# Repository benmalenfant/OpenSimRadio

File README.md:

# OpenSimRadio
Open sourced radio stack for flight simulation (Work in progress, not finished)

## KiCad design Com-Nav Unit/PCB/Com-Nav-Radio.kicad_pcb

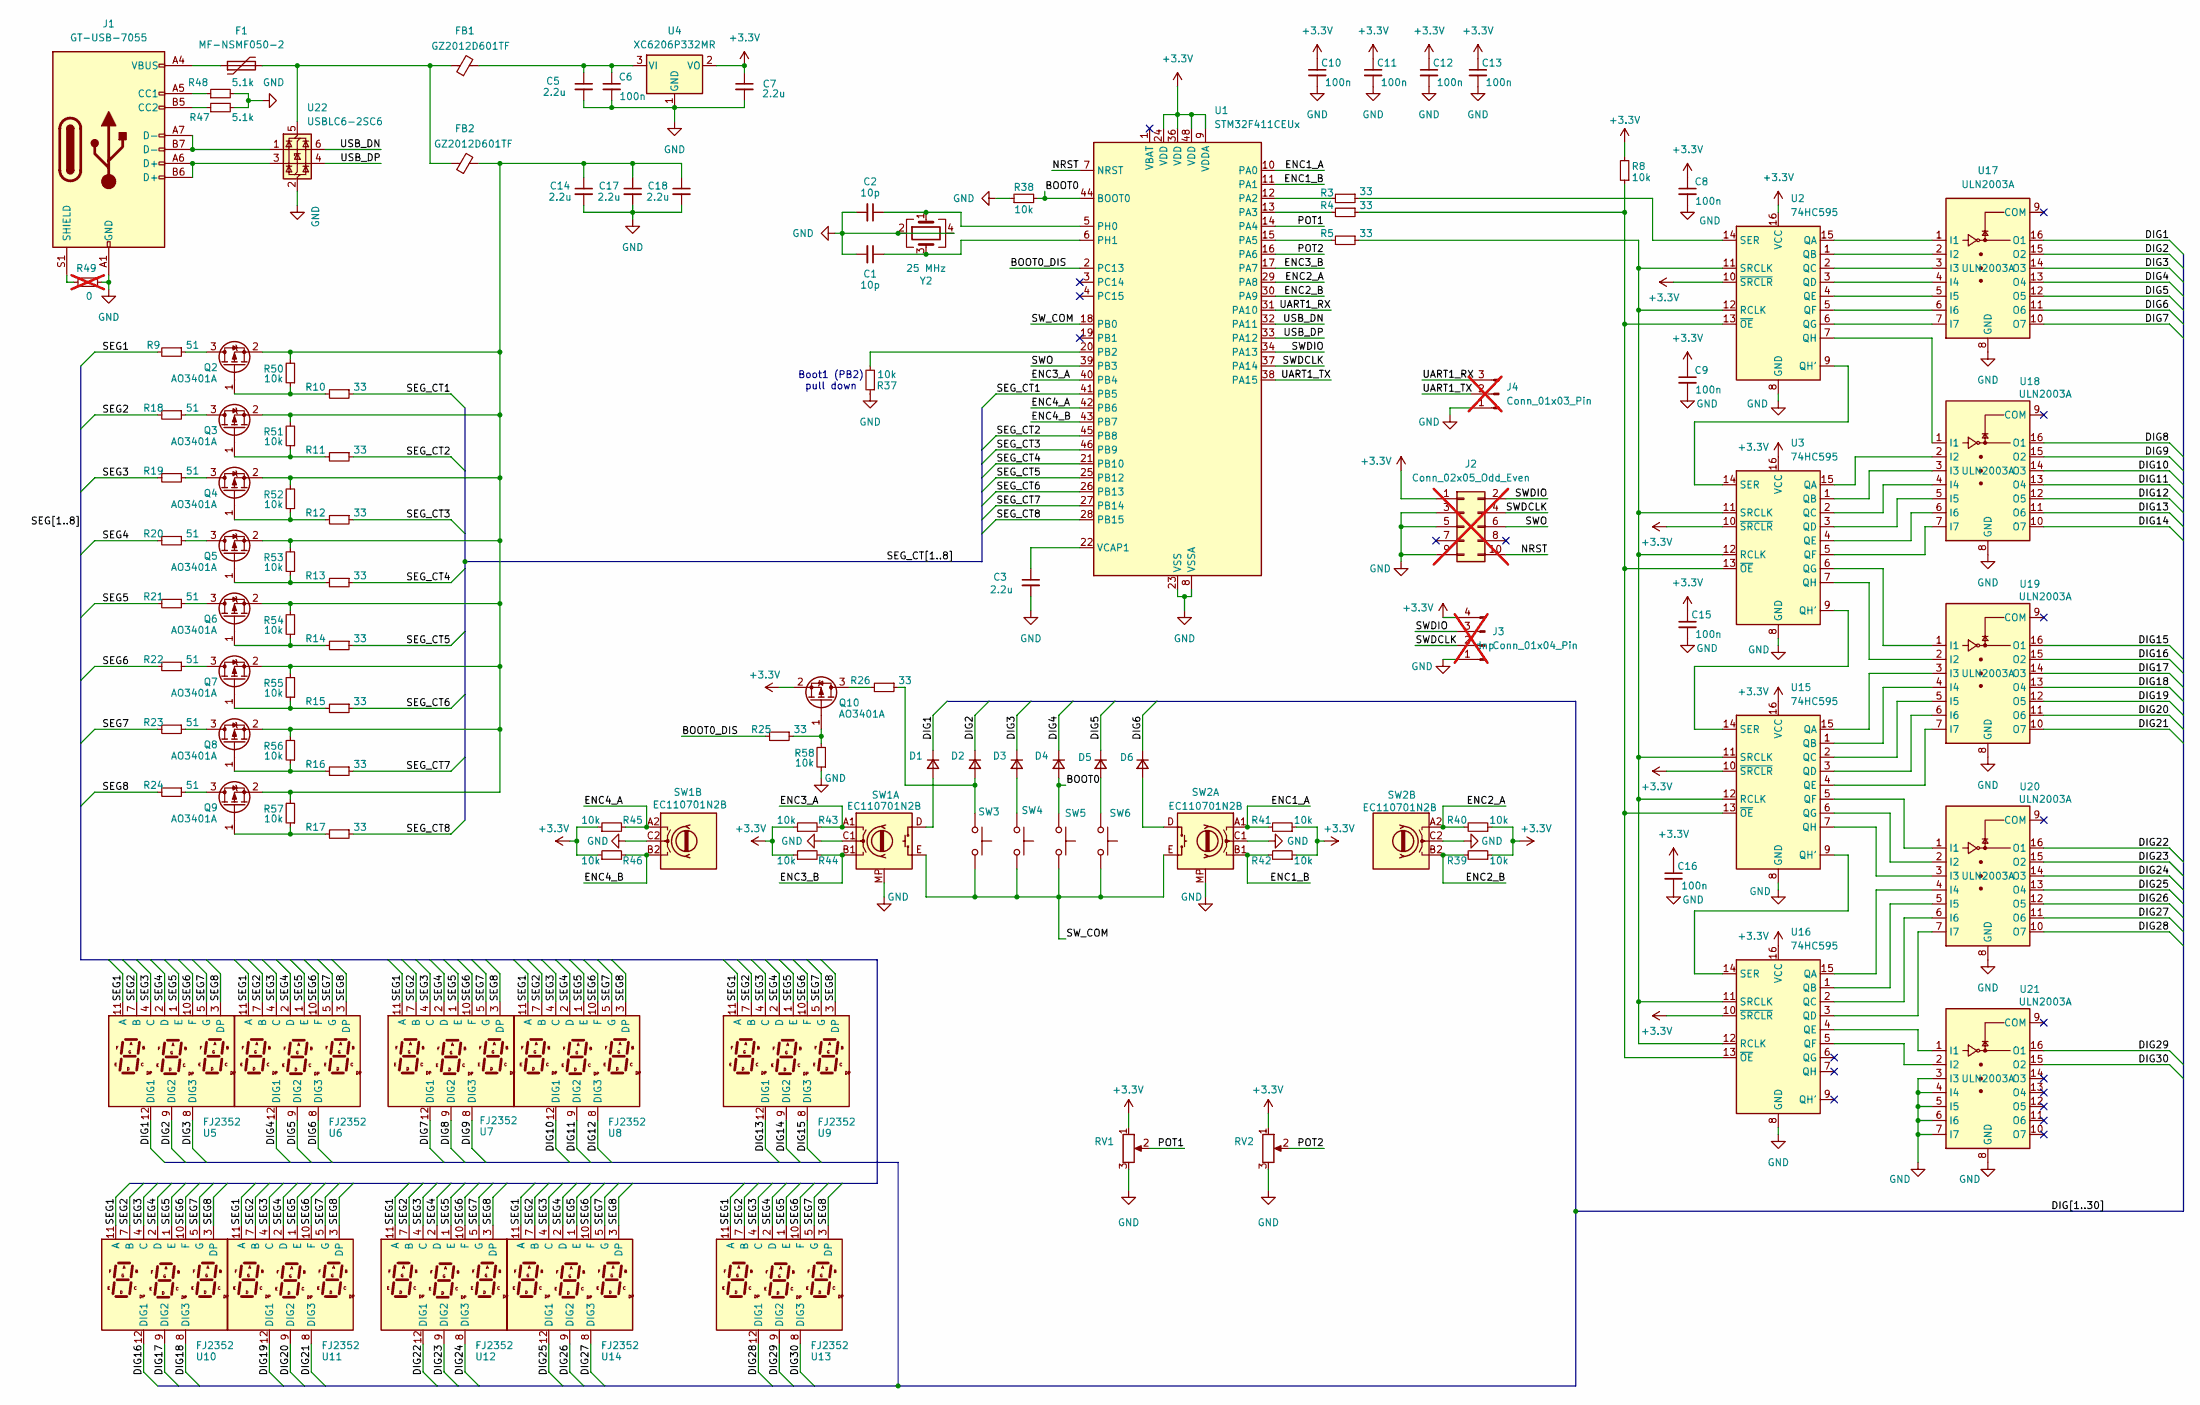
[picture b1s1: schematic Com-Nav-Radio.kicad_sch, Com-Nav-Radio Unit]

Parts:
C1, C2: 10p; C_0402_1005Metric
C3, C5, C7, C14, C17, C18: 2.2u; C_0603_1608Metric
C6, C8, C9, C10, C11, C12, C13, C15, C16: 100n; C_0402_1005Metric
D1, D2, D3, D4, D5, D6: 1N5819WS; D_SOD-323
F1: MF-NSMF050-2; Fuse_1206_3216Metric
FB1, FB2: GZ2012D601TF; L_0805_2012Metric
J1: GT-USB-7055; USB_C_Receptacle_G-Switch_GT-USB-7055x
J2: Conn_02x05_Odd_Even; PinHeader_2x05_P1.27mm_Vertical_SMD; not fitted
J3: Conn_01x04_Pin; PinHeader_1x04_P2.54mm_Vertical; not fitted
J4: Conn_01x03_Pin; PinHeader_1x03_P2.54mm_Vertical; not fitted
Q2, Q3, Q4, Q5, Q6, Q7, Q8, Q9, Q10: AO3401A; SOT-23
R3, R4, R5, R10, R11, R12, R13, R14, R15, R16, R17, R25, R26: 33; R_0402_1005Metric
R8, R37, R38, R39, R40, R41, R42, R43, R44, R45, R46, R50, R51, R52, R53, R54, R55, R56, R57, R58: 10k; R_0402_1005Metric
R9, R18, R19, R20, R21, R22, R23, R24: 51; R_0805_2012Metric
R47, R48: 5.1k; R_0402_1005Metric
R49: 0; R_0603_1608Metric; not fitted
RV1, RV2: RA0901N0X0D; RA0901N0X0D-HA1
SW1, SW2: EC110701N2B; EC11EBB24C03_EC110701N2B
SW3, SW4, SW5, SW6: SW_Push; SW_PUSH_6mm
U1: STM32F411CEUx; QFN-48-1EP_7x7mm_P0.5mm_EP5.6x5.6mm
U2, U3, U15, U16: 74HC595; SOIC-16_3.9x9.9mm_P1.27mm
U4: XC6206P332MR; SOT-23-3
U5, U6, U7, U8, U9, U10, U11, U12, U13, U14: FJ2352
U17, U18, U19, U20, U21: ULN2003A; SOIC-16_3.9x9.9mm_P1.27mm
U22: USBLC6-2SC6; SOT-23-6
Y2: 25 MHz; Crystal_SMD_3225-4Pin_3.2x2.5mm

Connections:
+3.3V: C7.1, C8.1, C9.1, C10.1, C11.1, C12.1, C13.1, C15.1, C16.1, J2.1, J3.4, Q10.2 (S), R8.2, R39.1, R40.1, R41.1, R42.1, R43.1, R44.1, R45.1, R46.1, RV1.1, RV2.1, U1.9 (VDDA), U1.24 (VDD), U1.36 (VDD), U1.48 (VDD), U2.10 (~SRCLR), U2.16 (VCC), U3.10 (~SRCLR), U3.16 (VCC), U4.2 (VO), U15.10 (~SRCLR), U15.16 (VCC), U16.10 (~SRCLR), U16.16 (VCC)
/BOOT0: D4.2 (A), R38.2, SW5.2, U1.44 (BOOT0)
/DIG1: D1.1 (K), U5.12 (DIG1), U17.16 (O1)
/DIG2: D2.1 (K), U5.9 (DIG2), U17.15 (O2)
/DIG3: D3.1 (K), U5.8 (DIG3), U17.14 (O3)
/DIG4: D4.1 (K), U6.12 (DIG1), U17.13 (O4)
/DIG5: D5.1 (K), U6.9 (DIG2), U17.12 (O5)
/DIG6: D6.1 (K), U6.8 (DIG3), U17.11 (O6)
/DIG7: U7.12 (DIG1), U17.10 (O7)
/DIG8: U7.9 (DIG2), U18.16 (O1)
/DIG9: U7.8 (DIG3), U18.15 (O2)
/DIG10: U8.12 (DIG1), U18.14 (O3)
/DIG11: U8.9 (DIG2), U18.13 (O4)
/DIG12: U8.8 (DIG3), U18.12 (O5)
/DIG13: U9.12 (DIG1), U18.11 (O6)
/DIG14: U9.9 (DIG2), U18.10 (O7)
/DIG15: U9.8 (DIG3), U19.16 (O1)
/DIG16: U10.12 (DIG1), U19.15 (O2)
/DIG17: U10.9 (DIG2), U19.14 (O3)
/DIG18: U10.8 (DIG3), U19.13 (O4)
/DIG19: U11.12 (DIG1), U19.12 (O5)
/DIG20: U11.9 (DIG2), U19.11 (O6)
/DIG21: U11.8 (DIG3), U19.10 (O7)
/DIG22: U12.12 (DIG1), U20.16 (O1)
/DIG23: U12.9 (DIG2), U20.15 (O2)
/DIG24: U12.8 (DIG3), U20.14 (O3)
/DIG25: U14.12 (DIG1), U20.13 (O4)
/DIG26: U14.9 (DIG2), U20.12 (O5)
/DIG27: U14.8 (DIG3), U20.11 (O6)
/DIG28: U13.12 (DIG1), U20.10 (O7)
/DIG29: U13.9 (DIG2), U21.16 (O1)
/DIG30: U13.8 (DIG3), U21.15 (O2)
/ENC1_A: R41.2, SW2.A1, U1.10 (PA0)
/ENC1_B: R42.2, SW2.B1, U1.11 (PA1)
/ENC2_A: R40.2, SW2.A2, U1.29 (PA8)
/ENC2_B: R39.2, SW2.B2, U1.30 (PA9)
/ENC3_A: R43.2, SW1.A1, U1.40 (PB4)
/ENC3_B: R44.2, SW1.B1, U1.17 (PA7)
/ENC4_A: R45.2, SW1.A2, U1.42 (PB6)
/ENC4_B: R46.2, SW1.B2, U1.43 (PB7)
/NRST: J2.10, U1.7 (NRST)
/POT1: RV1.2, U1.14 (PA4)
/POT2: RV2.2, U1.16 (PA6)
/SEG1: R9.2, U5.11 (A), U6.11 (A), U7.11 (A), U8.11 (A), U9.11 (A), U10.11 (A), U11.11 (A), U12.11 (A), U13.11 (A), U14.11 (A)
/SEG2: R18.2, U5.7 (B), U6.7 (B), U7.7 (B), U8.7 (B), U9.7 (B), U10.7 (B), U11.7 (B), U12.7 (B), U13.7 (B), U14.7 (B)
/SEG3: R19.2, U5.4 (C), U6.4 (C), U7.4 (C), U8.4 (C), U9.4 (C), U10.4 (C), U11.4 (C), U12.4 (C), U13.4 (C), U14.4 (C)
/SEG4: R20.2, U5.2 (D), U6.2 (D), U7.2 (D), U8.2 (D), U9.2 (D), U10.2 (D), U11.2 (D), U12.2 (D), U13.2 (D), U14.2 (D)
/SEG5: R21.2, U5.1 (E), U6.1 (E), U7.1 (E), U8.1 (E), U9.1 (E), U10.1 (E), U11.1 (E), U12.1 (E), U13.1 (E), U14.1 (E)
/SEG6: R22.2, U5.10 (F), U6.10 (F), U7.10 (F), U8.10 (F), U9.10 (F), U10.10 (F), U11.10 (F), U12.10 (F), U13.10 (F), U14.10 (F)
/SEG7: R23.2, U5.5 (G), U6.5 (G), U7.5 (G), U8.5 (G), U9.5 (G), U10.5 (G), U11.5 (G), U12.5 (G), U13.5 (G), U14.5 (G)
/SEG8: R24.2, U5.3 (DP), U6.3 (DP), U7.3 (DP), U8.3 (DP), U9.3 (DP), U10.3 (DP), U11.3 (DP), U12.3 (DP), U13.3 (DP), U14.3 (DP)
/SEG_CT1: R10.1, U1.41 (PB5)
/SEG_CT2: R11.1, U1.45 (PB8)
/SEG_CT3: R12.1, U1.46 (PB9)
/SEG_CT4: R13.1, U1.21 (PB10)
/SEG_CT5: R14.1, U1.25 (PB12)
/SEG_CT6: R15.1, U1.26 (PB13)
/SEG_CT7: R16.1, U1.27 (PB14)
/SEG_CT8: R17.1, U1.28 (PB15)
/SWDCLK: J2.4, J3.2, U1.37 (PA14)
/SWDIO: J2.2, J3.3, U1.34 (PA13)
/SWO: J2.6, U1.39 (PB3)
/SW_COM: SW1.E, SW2.E, SW3.1, SW4.1, SW5.1, SW6.1, U1.18 (PB0)
/USB_DN: U1.32 (PA11), U22.6 (I/O1)
/USB_DP: U1.33 (PA12), U22.4 (I/O2)
GND: C1.2, C2.2, C3.2, C5.2, C6.2, C7.2, C8.2, C9.2, C10.2, C11.2, C12.2, C13.2, C14.2, C15.2, C16.2, C17.2, C18.2, J1.A1 (GND), J1.A12 (GND), J1.B1 (GND), J1.B12 (GND), J2.3, J2.5, J2.9, J3.1, J4.1, R37.1, R38.1, R47.2, R48.2, R49.2, R58.1, RV1.3, RV2.3, SW1.C1, SW1.C2, SW1.MP, SW2.C1, SW2.C2, SW2.MP, U1.8 (VSSA), U1.23 (VSS), U1.35 (VSS), U1.47 (VSS), U1.49 (VSS), U2.8 (GND), U3.8 (GND), U4.1 (GND), U15.8 (GND), U16.8 (GND), U17.8 (GND), U18.8 (GND), U19.8 (GND), U20.8 (GND), U21.3 (I3), U21.4 (I4), U21.5 (I5), U21.6 (I6), U21.7 (I7), U21.8 (GND), U22.2 (GND), Y2.2, Y2.4
unnamed: D1.2 (A), SW1.D
unnamed: D2.2 (A), R26.1, SW3.2
unnamed: D3.2 (A), SW4.2
unnamed: D5.2 (A), SW6.2
unnamed: D6.2 (A), SW2.D
unnamed: F1.1, J1.A4 (VBUS), J1.A9 (VBUS), J1.B4 (VBUS), J1.B9 (VBUS)
unnamed: J1.A5 (CC1), R48.1
unnamed: J1.B5 (CC2), R47.1
unnamed: J1.A6 (D+), J1.B6 (D+), U22.3 (I/O2)
unnamed: J1.A7 (D-), J1.B7 (D-), U22.1 (I/O1)
unnamed: J1.S1 (SHIELD), R49.1
unnamed: J4.2, U1.38 (PA15)
unnamed: J4.3, U1.31 (PA10)
unnamed: Q2.3 (D), R9.1
unnamed: Q2.1 (G), R10.2, R50.1
unnamed: C14.1, C17.1, C18.1, FB2.2, Q2.2 (S), Q3.2 (S), Q4.2 (S), Q5.2 (S), Q6.2 (S), Q7.2 (S), Q8.2 (S), Q9.2 (S), R50.2, R51.2, R52.2, R53.2, R54.2, R55.2, R56.2, R57.2
unnamed: Q3.3 (D), R18.1
unnamed: Q3.1 (G), R11.2, R51.1
unnamed: Q4.3 (D), R19.1
unnamed: Q4.1 (G), R12.2, R52.1
unnamed: Q5.3 (D), R20.1
unnamed: Q5.1 (G), R13.2, R53.1
unnamed: Q6.3 (D), R21.1
unnamed: Q6.1 (G), R14.2, R54.1
unnamed: Q7.3 (D), R22.1
unnamed: Q7.1 (G), R15.2, R55.1
unnamed: Q8.3 (D), R23.1
unnamed: Q8.1 (G), R16.2, R56.1
unnamed: Q9.3 (D), R24.1
unnamed: Q9.1 (G), R17.2, R57.1
unnamed: Q10.3 (D), R26.2
unnamed: R3.2, U1.12 (PA2)
unnamed: R4.2, U1.13 (PA3)
unnamed: R5.2, U1.15 (PA5)
unnamed: R37.2, U1.20 (PB2)
unnamed: C2.1, U1.5 (PH0), Y2.1
unnamed: C1.1, U1.6 (PH1), Y2.3
unnamed: C3.1, U1.22 (VCAP1)
unnamed: U2.9 (QH'), U3.14 (SER)
unnamed: R3.1, U2.14 (SER)
unnamed: C5.1, C6.1, FB1.2, U4.3 (VI)
unnamed: U15.15 (QA), U19.3 (I3)
unnamed: U15.1 (QB), U19.4 (I4)
unnamed: U15.2 (QC), U19.5 (I5)
unnamed: U15.3 (QD), U19.6 (I6)
unnamed: U15.4 (QE), U19.7 (I7)
unnamed: U15.5 (QF), U20.1 (I1)
unnamed: U15.6 (QG), U20.2 (I2)
unnamed: U15.9 (QH'), U16.14 (SER)
unnamed: U15.7 (QH), U20.3 (I3)
unnamed: R5.1, U2.11 (SRCLK), U2.12 (RCLK), U3.11 (SRCLK), U3.12 (RCLK), U15.11 (SRCLK), U15.12 (RCLK), U16.11 (SRCLK), U16.12 (RCLK)
unnamed: U3.9 (QH'), U15.14 (SER)
unnamed: R4.1, R8.1, U2.13 (~OE), U3.13 (~OE), U15.13 (~OE), U16.13 (~OE)
unnamed: U16.15 (QA), U20.4 (I4)
unnamed: U16.1 (QB), U20.5 (I5)
unnamed: U16.2 (QC), U20.6 (I6)
unnamed: U16.3 (QD), U20.7 (I7)
unnamed: U16.4 (QE), U21.1 (I1)
unnamed: U16.5 (QF), U21.2 (I2)
unnamed: U2.15 (QA), U17.1 (I1)
unnamed: U2.1 (QB), U17.2 (I2)
unnamed: U2.2 (QC), U17.3 (I3)
unnamed: U2.3 (QD), U17.4 (I4)
unnamed: U2.4 (QE), U17.5 (I5)
unnamed: U2.5 (QF), U17.6 (I6)
unnamed: U2.6 (QG), U17.7 (I7)
unnamed: U2.7 (QH), U18.1 (I1)
unnamed: U3.15 (QA), U18.2 (I2)
unnamed: U3.1 (QB), U18.3 (I3)
unnamed: U3.2 (QC), U18.4 (I4)
unnamed: U3.3 (QD), U18.5 (I5)
unnamed: U3.4 (QE), U18.6 (I6)
unnamed: U3.5 (QF), U18.7 (I7)
unnamed: U3.6 (QG), U19.1 (I1)
unnamed: U3.7 (QH), U19.2 (I2)
unnamed: F1.2, FB1.1, FB2.1, U22.5 (VBUS)

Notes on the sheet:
Boot1 (PB2) pull down

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
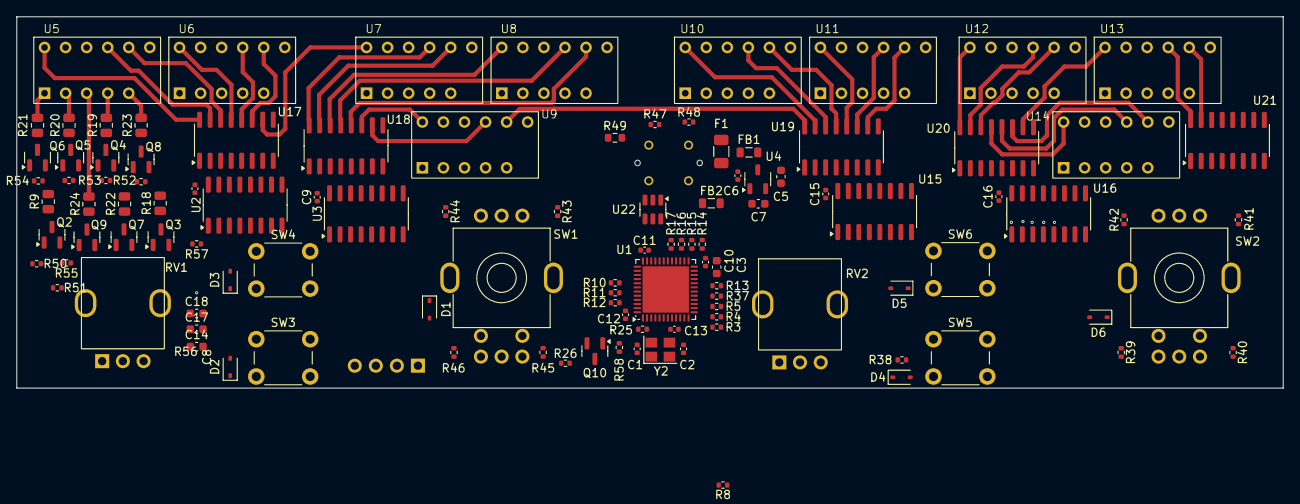
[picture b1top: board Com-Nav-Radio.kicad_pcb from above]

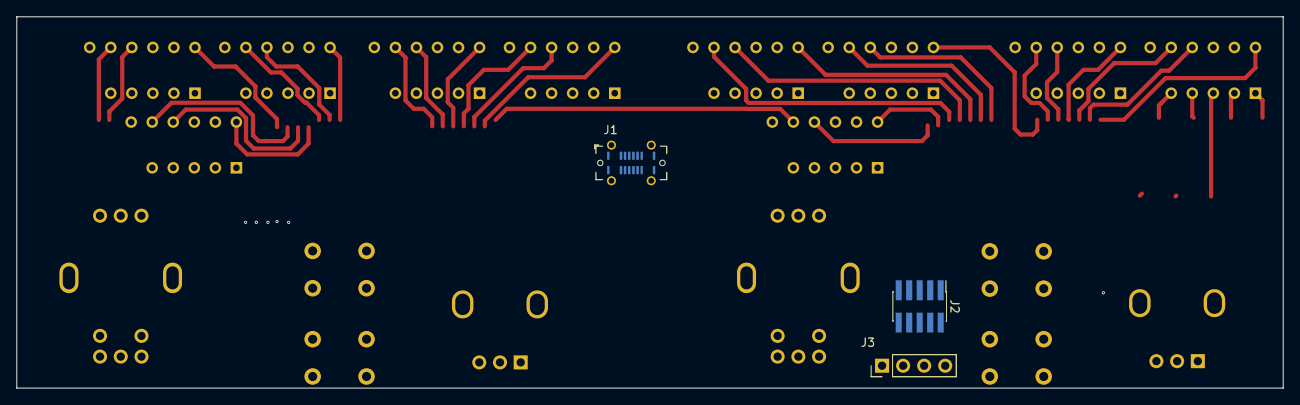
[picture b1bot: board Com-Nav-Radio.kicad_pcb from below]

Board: 4 copper layers, 152.8 x 44.8 mm, 113 parts (3 on the bottom side), 142 nets.

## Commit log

2020-10-06 Initial commit
    MCU page mostly done
2025-03-16 Demo firmware for timers
2025-03-16 Firmware working daisy chaining
2025-03-16 Firmware - work on timings for the displays
2025-03-16 Firmware - Display timers complete, missing the digit update function
2025-03-16 Firmware, update refresh rate to 1kHz
2025-03-16 Mechanical - First draft for 7 segment placement
2025-03-16 Firmware - Invert data polarity since we are using common anode
2025-03-16 Firmware - Changed Timings to allow time for the interrupt, might consider DMA in the future
2025-03-16 Hardware - Add notes including the part choices
2025-03-18 PCB - Work on schematic
2025-03-19 PCB- Sch Connect 7 segments
2025-03-22 add swdio to stm in sch, add fab outputs to gitignore
2025-04-01 PCB - Add ferite bead, connect encoders
2025-04-06 PCB - Changed to common cathode with 2 more shift reg
2025-04-06 FW - Change clock/data pins
2025-04-18 PCB - Add swd connector, add switches
2025-04-18 PCB - SCH - first drc run, add no connect flags
2025-05-03 PCB - work on schematic, initial board placement
2025-05-04 PCB - Sketch routing of the 7 segments
2026-04-10 Update project status in README
